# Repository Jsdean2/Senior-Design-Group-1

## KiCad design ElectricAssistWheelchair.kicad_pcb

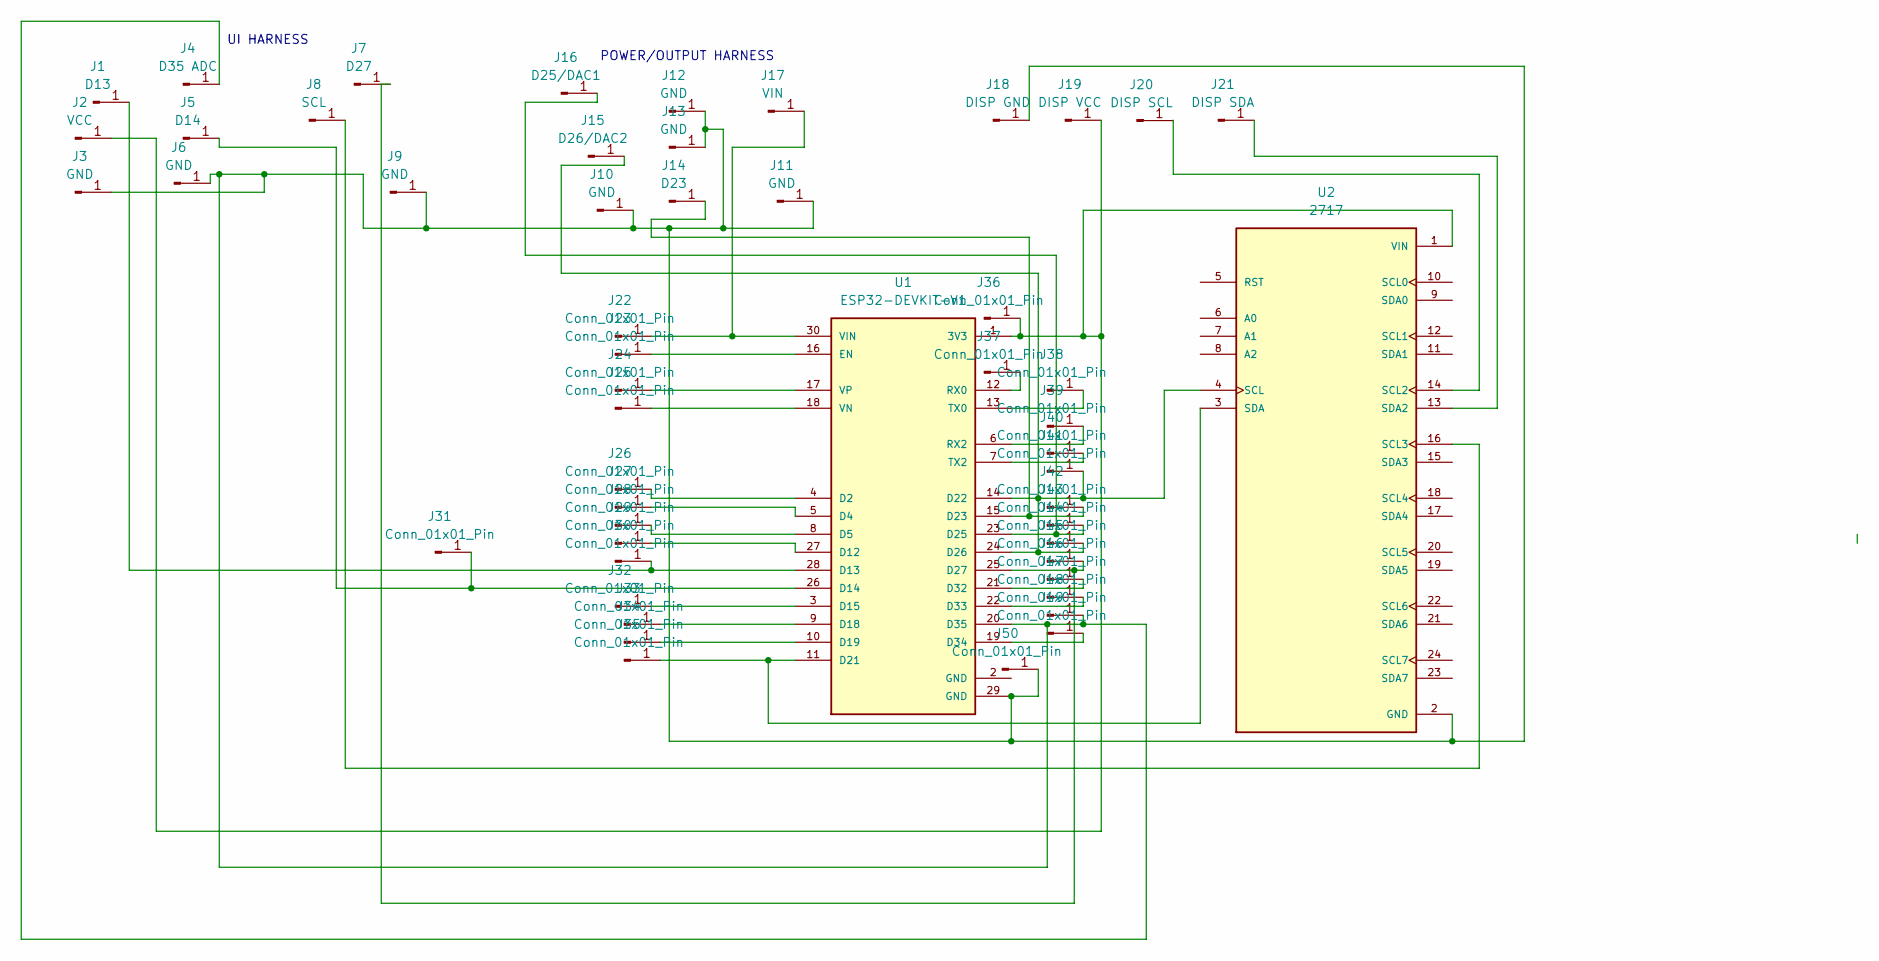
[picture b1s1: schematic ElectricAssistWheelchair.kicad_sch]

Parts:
J1: D13; PinHeader_1x01_P2.54mm_Vertical
J2: VCC; PinHeader_1x01_P2.54mm_Vertical
J3, J6, J9, J10, J11, J12, J13: GND; PinHeader_1x01_P2.54mm_Vertical
J4: D35 ADC; PinHeader_1x01_P2.54mm_Vertical
J5: D14; PinHeader_1x01_P2.54mm_Vertical
J7: D27; PinHeader_1x01_P2.54mm_Vertical
J8: SCL; PinHeader_1x01_P2.54mm_Vertical
J14: D23; PinHeader_1x01_P2.54mm_Vertical
J15: D26/DAC2; PinHeader_1x01_P2.54mm_Vertical
J16: D25/DAC1; PinHeader_1x01_P2.54mm_Vertical
J17: VIN; PinHeader_1x01_P2.54mm_Vertical
J18: DISP GND; PinSocket_1x01_P2.54mm_Vertical
J19: DISP VCC; PinSocket_1x01_P2.54mm_Vertical
J20: DISP SCL; PinSocket_1x01_P2.54mm_Vertical
J21: DISP SDA; PinSocket_1x01_P2.54mm_Vertical
J22, J23, J24, J25, J26, J27, J28, J29, J30, J31, J32, J33, J34, J35, J36, J37, J38, J39, J40, J41, J42, J43, J44, J45, J46, J47, J48, J49, J50: Conn_01x01_Pin; PinSocket_1x01_P2.54mm_Vertical
U1: ESP32-DEVKIT-V1; MODULE_ESP32_DEVKIT_V1; PARTREV N/A
U2: 2717; MODULE_2717; PARTREV Sep 11, 2015

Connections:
unnamed: J1.1, J30.1, U1.28 (D13)
unnamed: J8.1, U2.16 (SCL3)
unnamed: J3.1, J4.1, J6.1, J9.1, J10.1, J11.1, J12.1, J13.1, J18.1, J48.1, J50.1, U1.20 (D35), U1.29 (GND), U2.2 (GND)
unnamed: J14.1, J42.1, U1.15 (D23)
unnamed: J15.1, J41.1, J44.1, U1.14 (D22), U1.24 (D26), U2.4 (SCL)
unnamed: J16.1, J43.1, U1.23 (D25)
unnamed: J17.1, J22.1, U1.30 (VIN)
unnamed: J2.1, J19.1, J36.1, U1.1 (3V3), U2.1 (VIN)
unnamed: J21.1, U2.13 (SDA2)
unnamed: J23.1, U1.16 (EN)
unnamed: J24.1, U1.17 (VP)
unnamed: J25.1, U1.18 (VN)
unnamed: J26.1, U1.4 (D2)
unnamed: J27.1, U1.5 (D4)
unnamed: J28.1, U1.8 (D5)
unnamed: J29.1, U1.27 (D12)
unnamed: J5.1, J31.1, U1.26 (D14)
unnamed: J32.1, U1.3 (D15)
unnamed: J33.1, U1.9 (D18)
unnamed: J34.1, U1.10 (D19)
unnamed: J35.1, U1.11 (D21), U2.3 (SDA)
unnamed: J37.1, U1.12 (RX0)
unnamed: J38.1, U1.13 (TX0)
unnamed: J39.1, U1.6 (RX2)
unnamed: J40.1, U1.7 (TX2)
unnamed: J7.1, J45.1, U1.25 (D27)
unnamed: J46.1, U1.21 (D32)
unnamed: J47.1, U1.22 (D33)
unnamed: J49.1, U1.19 (D34)

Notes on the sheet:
POWER/OUTPUT HARNESS
UI HARNESS

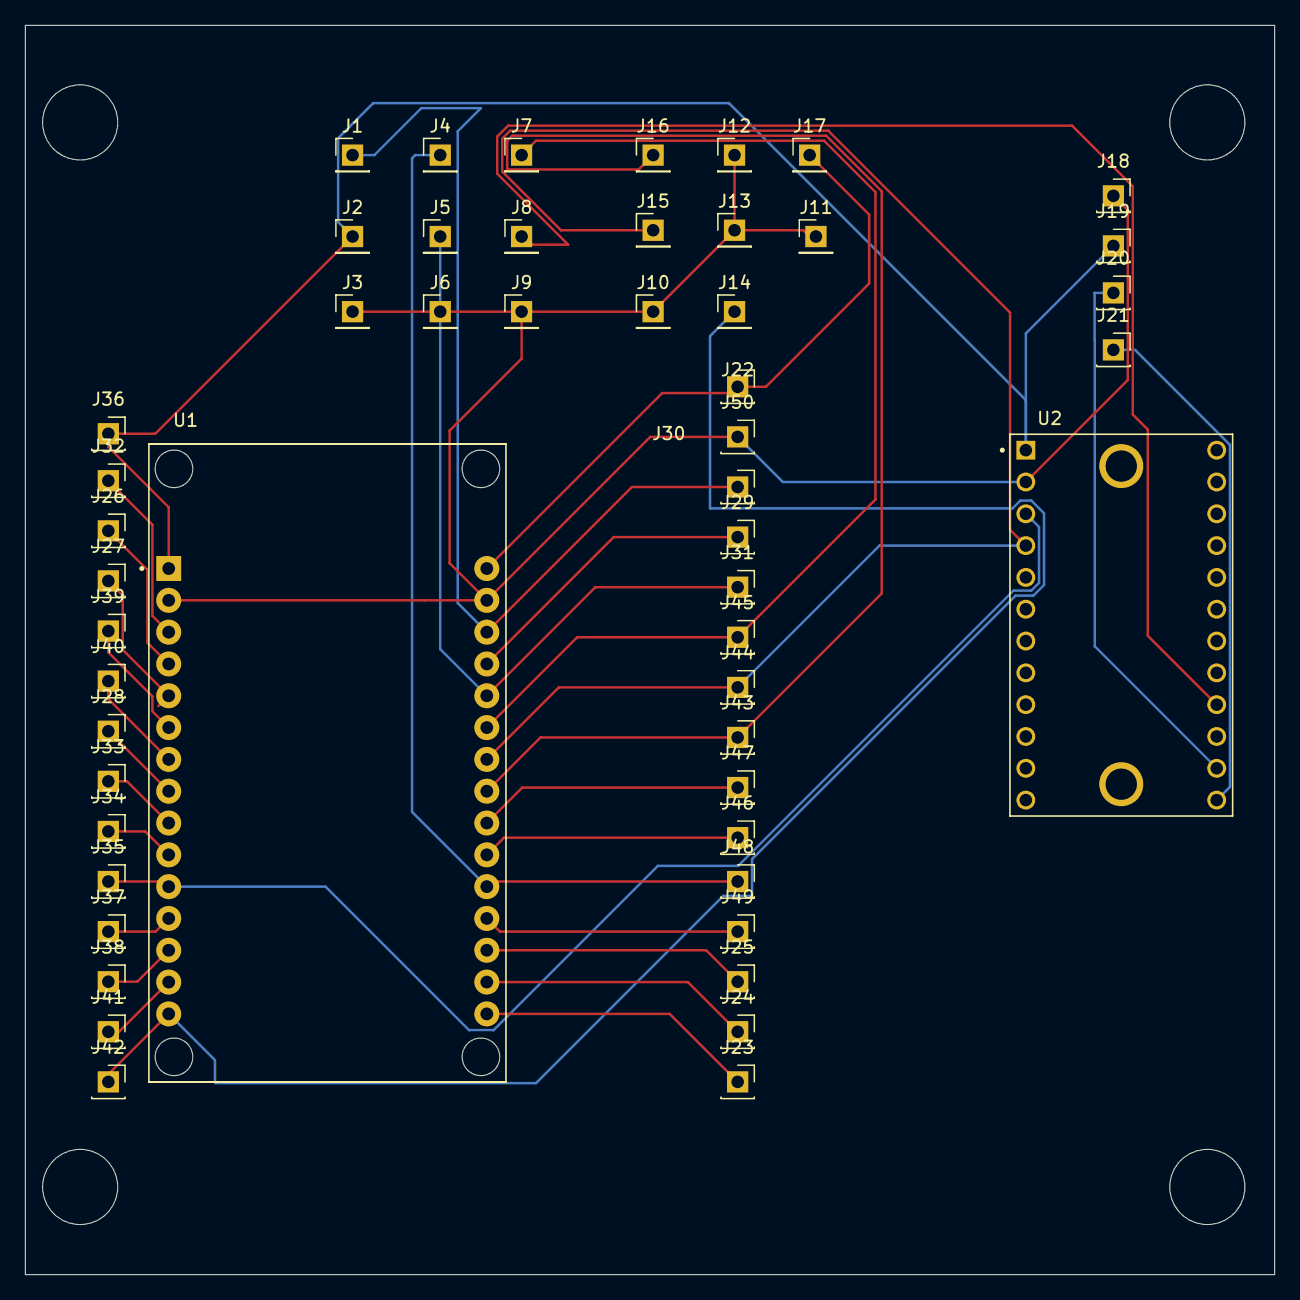
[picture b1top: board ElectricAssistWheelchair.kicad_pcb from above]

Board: 2 copper layers, 99.8 x 99.8 mm, 52 parts (0 on the bottom side), 29 nets.

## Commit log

2025-01-17 PCB- mel
2025-01-17 PCB- mel - finished
